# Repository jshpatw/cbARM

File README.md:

# cbARM (Cheese Burger ARM)

A 5-DOF (Degrees of Freedom) robot arm designed for high scalability, low cost, and ease of assembly using common makerspace materials.

## Why did i make this?

I always wanted an interactable robotic arm. But, online, the cheap ones cant lift any substancial weight and the good ones are very unaffordable. Most arms also came in fixed sizes and usally had a short range of motion. By making this prodject, I hope to adress theese 3 problems.

## Project Overview

The cbARM project aims to recreate industry-standard robot arm functionality using affordable, accessible components. By utilizing NEMA 17 motors, 3D-printed planetary gearboxes, a fully 3d printed conical stylle thrust bearing, and 2020 aluminum extrusions, this project provides a modular, affordable, and highly repairable alternative to commercial robotic systems.

## Target Features

* 5 Degrees of Freedom for full spatial maneuverability.
* Accessible build requiring no specialized machining.
* Modular design utilizing 2020 aluminum extrusions for variable arm lengths.
* Modular electronics; using female sockets soldered onto the pcb for "hot swapping" and easy electronics replacement.
* Scalable architecture for easy repair and upgrades.

## [Bill of Materials (BOM)]([url](https://github.com/jshpatw/cbARM/blob/main/BOM.csv))
u can find the bom in the repo via BOM.csv 

## Assembly and CAD Files

All STL files required for 3D printing the chassis and planetary gearboxes are available in the `/stl` directory of this repository. Refer to the pictures in journal.md portion for more complex parts and to see how I went about making things

* Recommended Material: PETG; 3 or more wall loops 20% minimum density 100% for gears and parts holding torque and gyroid pattern for structural rigidity and heat resistance (feel free to use PLA and other settings to test fitments).
* Hardware: Ensure all M3 heat-set inserts are installed prior to joining arm segments. 
* Bearings: Ensure 10x5x4mm bearings are seated with light pressure to avoid binding within 3D-printed pockets.
* Remember to practice safety when soldering parts and make sure to get extras and expect electronic defects.

Above is are pictures of the final PCB design for the prodject as of now. I reccomend using solder on female sockets to achive the electronic modularity. ensure u plug the 24V cables the right way as to not fry the board...

 The J0 objects mainly feature:
* Mounting holes for the 2020 extrution
* A vertical mount for the nema 17 42HS60
* 16:1 planetary reducers
* A 160mm 16 pin thrust bearing inspired by Logic [Planets work]([url](https://thangs.com/designer/logicalplanet/3d-model/Lazy%20Susan%20160%20v3.0-1514462))

He also has a youtube video in that link, I recommend watching his videos to better understand the mechanics and how to assemble that specific part.

 The J1 objects feature:
* A horizontal mount for the nema 17 hs 60 motor
* A 64:1 planetary gearbox
* Specialized thick gears to hendle the high torque setup
* A ring gear with a 2020 extrution mount for torque output

Above shows how the arm should look like after the 3d printed parts are assembled. (note that wires and electronics arent shown in this picture.

I made a document specially for assembly instructions at assembly guide.md in the repo for more in depth instructions and for the rest of the parts.

## Firmware and Control
 
* Status: Development in progress. 
* Firmware: To be updated.
* Control Interface: To be updated.

DISCLAIMER: the code is still physically untested so joints may move not as intended

## Future Roadmap

* Integration of Inverse Kinematics (IK) libraries.
* Development of end-effector/gripper attachments.
* Optimization of planetary gearbox backlash and tolerances.

## Extra info
* The CAD softwares used to make the prodject are KiCad and Fusion360 on education license
* Im using a p2s for prototyping and printing parts
* I also used pla to test initial fitments and tolerances
* I used old arduino code as reference and made the scripts on vs code and double checked with chatgpt
### Links & sources:
* https://thangs.com/designer/logicalplanet/3d-model/Lazy%20Susan%20160%20v3.0-1514462
* https://www.youtube.com/watch?v=S1EmJKU_IJU
* https://makerworld.com/en/models/2686085-planetary-gearbox-nema-17-1-16

## Feedback

Im currently doing everything solo so im open for advice and would appreciate feedback regarding anything in the prodject. 

## License

This project is licensed under the MIT License.

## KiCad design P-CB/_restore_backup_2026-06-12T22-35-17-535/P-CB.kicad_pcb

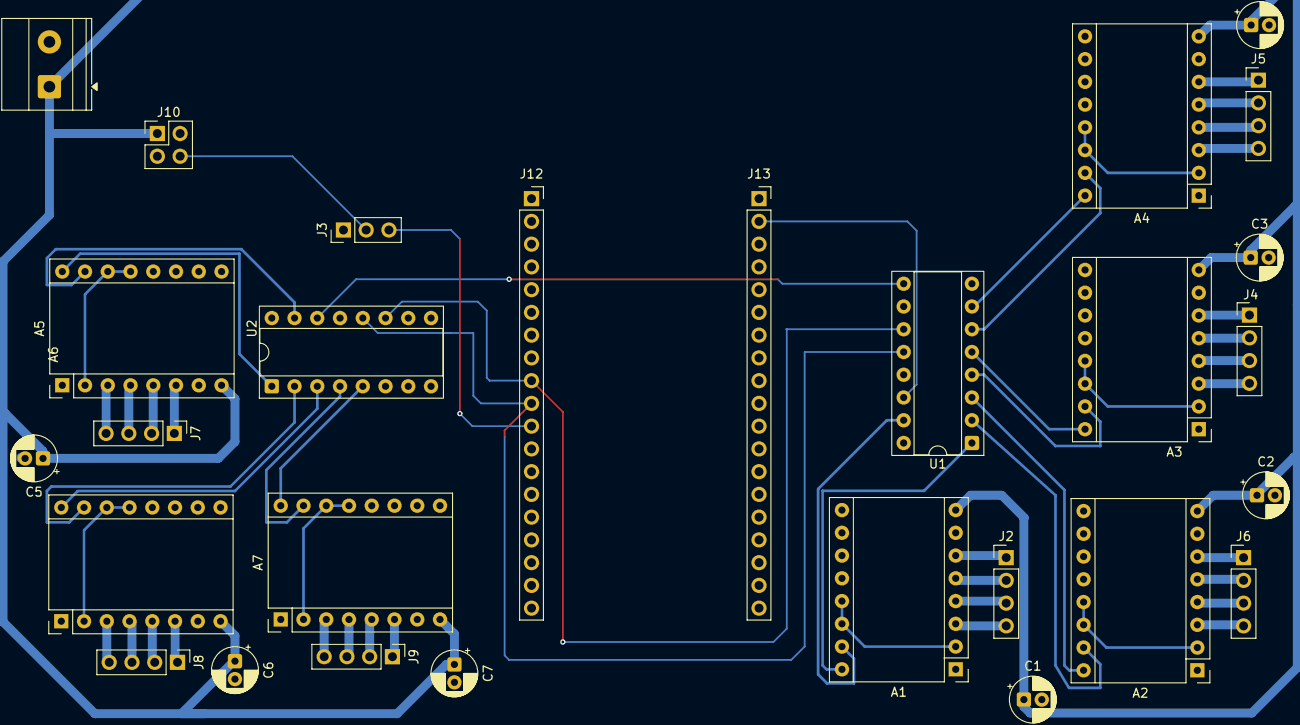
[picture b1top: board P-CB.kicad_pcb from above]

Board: 2 copper layers, 28 parts (0 on the bottom side), 51 nets.

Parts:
A1, A2, A3, A4, A5, A6, A7: Pololu_Breakout_A4988; Pololu_Breakout-16_15.2x20.3mm
C1, C2, C3, C4, C5, C6, C7: C_Polarized; CP_Radial_D5.0mm_P2.00mm
J2, J4, J5, J6, J7, J8, J9: Conn_01x04_Pin; PinHeader_1x04_P2.54mm_Vertical
J3: Conn_01x03; PinHeader_1x03_P2.54mm_Vertical
J10: Conn_02x02_Counter_Clockwise; PinHeader_2x02_P2.54mm_Vertical
J11: Conn_01x02_Pin; TerminalBlock_Phoenix_MKDS-1,5-2_1x02_P5.00mm_Horizontal
J12, J13: Conn_01x19; PinSocket_1x19_P2.54mm_Vertical
U1, U2: 74HC595; DIP-16_W7.62mm_Socket

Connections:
+5V: J3.2, J10.4, J13.1
+24V: A1.8 (VMOT), A2.8 (VMOT), A3.8 (VMOT), A4.8 (VMOT), A5.8 (VMOT), A6.8 (VMOT), A7.8 (VMOT), C1.1, C2.1, C3.1, C4.1, C5.1, C6.1, C7.1, J10.1, J11.1
/3.3V_global: A1.2 (VDD), A1.13 (~RESET), A1.14 (~SLEEP), A2.2 (VDD), A2.13 (~RESET), A2.14 (~SLEEP), A3.2 (VDD), A3.13 (~RESET), A3.14 (~SLEEP), A4.2 (VDD), A4.13 (~RESET), A4.14 (~SLEEP), A5.2 (VDD), A5.13 (~RESET), A5.14 (~SLEEP), A6.2 (VDD), A6.13 (~RESET), A6.14 (~SLEEP), A7.2 (VDD), A7.13 (~RESET), A7.14 (~SLEEP), J12.1, U1.10 (~SRCLR), U1.16 (VCC), U2.10 (~SRCLR), U2.16 (VCC)
/DATA_CASCADE: U1.9 (QH'), U2.14 (SER)
/I2S_BCK: J12.9, U1.11 (SRCLK), U2.11 (SRCLK)
/I2S_DATA: J13.2, U1.14 (SER)
/I2S_LATCH: J12.10, U1.12 (RCLK), U2.12 (RCLK)
/SERVO_PWM: J3.3, J12.11
GND: A1.1 (GND), A1.7 (GND), A2.1 (GND), A2.7 (GND), A3.1 (GND), A3.7 (GND), A4.1 (GND), A4.7 (GND), A5.1 (GND), A5.7 (GND), A6.1 (GND), A6.7 (GND), A7.1 (GND), A7.7 (GND), J3.1, J10.2, J10.3, J11.2, J13.19, U1.8 (GND), U1.13 (~OE), U2.8 (GND), U2.13 (~OE)
unnamed: A1.4 (1A), J2.3
unnamed: A1.3 (1B), J2.4
unnamed: A1.5 (2A), J2.2
unnamed: A1.6 (2B), J2.1
unnamed: A1.16 (DIR), U1.1 (QB)
unnamed: A1.15 (STEP), U1.15 (QA)
unnamed: A2.4 (1A), J6.3
unnamed: A2.3 (1B), J6.4
unnamed: A2.5 (2A), J6.2
unnamed: A2.6 (2B), J6.1
unnamed: A2.16 (DIR), U1.3 (QD)
unnamed: A2.15 (STEP), U1.2 (QC)
unnamed: A3.4 (1A), J4.3
unnamed: A3.3 (1B), J4.4
unnamed: A3.5 (2A), J4.2
unnamed: A3.6 (2B), J4.1
unnamed: A3.16 (DIR), U1.5 (QF)
unnamed: A3.15 (STEP), U1.4 (QE)
unnamed: A4.4 (1A), J5.3
unnamed: A4.3 (1B), J5.4
unnamed: A4.5 (2A), J5.2
unnamed: A4.6 (2B), J5.1
unnamed: A4.16 (DIR), U1.7 (QH)
unnamed: A4.15 (STEP), U1.6 (QG)
unnamed: A5.4 (1A), J7.3
unnamed: A5.3 (1B), J7.4
unnamed: A5.5 (2A), J7.2
unnamed: A5.6 (2B), J7.1
unnamed: A5.16 (DIR), U2.1 (QB)
unnamed: A5.15 (STEP), U2.15 (QA)
unnamed: A6.4 (1A), J8.3
unnamed: A6.3 (1B), J8.4
unnamed: A6.5 (2A), J8.2
unnamed: A6.6 (2B), J8.1
unnamed: A6.16 (DIR), U2.3 (QD)
unnamed: A6.15 (STEP), U2.2 (QC)
unnamed: A7.4 (1A), J9.3
unnamed: A7.3 (1B), J9.4
unnamed: A7.5 (2A), J9.2
unnamed: A7.6 (2B), J9.1
unnamed: A7.16 (DIR), U2.5 (QF)
unnamed: A7.15 (STEP), U2.4 (QE)

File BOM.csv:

"Category","Reference/Item","Qty","Value/Spec","Manufacturer/Notes"
"Electronics","A1-A7","7","Pololu_A4988","Motor Drivers"
"Electronics","C1-C7","7","100uF_35V","Electrolytic Capacitor"
"Electronics","J2,J4-J9","7","Conn_01x04","Header Pins"
"Electronics","J3","1","Conn_01x03","Header Pins"
"Electronics","J10","1","Mini360_Module","Buck Converter"
"Electronics","J11","1","2_Pin_Term_Block","5.00mm Pitch"
"Electronics","J12,J13","2","Conn_01x19","Pin Socket"
"Electronics","U1,U2","2","74HC595","Shift Register"
"Electronics","Power Supply","1","24V 15A","Main System PSU"
"Mechanical","Stepper Motors","7","NEMA 17 (42HS60)","1.8 Degree Step"
"Mechanical","Bearings","100","MR105ZZ (10x5x4mm)","Steel Shielded"
"Mechanical","Screws","100","M3 x 10mm","Socket Head Cap"
"Mechanical","Heat-Set Inserts","100","M3 Brass Insert","For PETG"
"Mechanical","Filament","3kg","PETG 1.75mm","Chassis Material"

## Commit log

2026-06-20 pcb stuff!
2026-06-20 most of the stls
2026-06-20 zine
    im sorry for for my lack of design skilss
2026-06-20 Add BOM.csv with components and specifications
2026-06-20 Enhance README with project details and instructions
    Added detailed project overview, target features, bill of materials, assembly instructions, firmware status, future roadmap, and feedback section to README.
2026-06-20 Include PCB design images and project status update
    Added images of the final PCB design and updated project status.
2026-06-20 Update README with PCB design images and status
    Added a note about the final PCB design and firmware status.
2026-06-20 Add Firmware and Control section to README
    Added section for Firmware and Control status updates.
2026-06-20 Update README with PCB and arm assembly images
    Added images of the final PCB design and 3D printed arm assembly.
2026-06-21 Update README with modular electronics details
    Added information about modular electronics and provided recommendations for soldering female sockets to achieve electronic modularity.
2026-06-22 Revise README with material and assembly details
    Updated material specifications and added details about J0 objects.
2026-06-22 Enhance README with assembly video recommendation
    Added a recommendation to watch a YouTube video for better understanding of assembly.
2026-06-25 Add assembly guide for cbARM PCB and housing
    This guide provides detailed instructions for assembling the cbARM control module, including PCB and electronics setup, connector configurations, mounting, and pre-power inspection steps.
2026-06-25 Enhance assembly guide for J0 parts
    Expanded assembly instructions for J0 parts, including details on aluminum extrusions and motor mounting.
2026-06-25 Update assembly guide with j0 component details
    Clarified assembly instructions for j0 component, including recommendations for aluminum extrusion lengths and motor mounting.
2026-06-25 Enhance assembly guide with thrust bearing instructions
    Added detailed instructions for assembling the thrust bearing and j0 components, including references to specific STL files and images for clarity.
2026-06-25 Revise thrust bearing assembly instructions
    Updated assembly instructions for thrust bearing and j0 components, including new image references.
2026-06-26 zine
2026-06-26 Rename Copy of Chese burger-1.pdf to Chese burger.pdf
2026-06-26 Replace image of cbARM with updated version
    Updated image reference in README.md to a new source.
2026-06-27 Document J1 assembly instructions and parts list
    Added detailed instructions for assembling J1 parts, including a list of components and assembly steps.
2026-06-27 Enhance assembly guide with J2 supports and parts
    Added detailed instructions for J2 supports and parts assembly.
2026-06-27 Update BOM.csv to correct component description
2026-06-27 Fix typos in assembly guide for bearing sizes
2026-06-28 Add Google Drive link for CAD files
2026-06-28 Add files via upload
    firmware for testing upon assembly
2026-06-28 Fix CSV header formatting in BOM.csv
2026-06-28 Duplicate entries added to BOM.csv
    Added duplicate entries for various components in BOM.csv.
2026-06-28 Revise BOM with updated item specifications and pricing
    Updated BOM.csv to include new pricing and item details.
2026-06-28 Revise BOM section and add assembly guide reference
    Updated Bill of Materials section and added assembly instructions note.
2026-06-28 Add second image to README for cbARM project
    Added a second image of the cbARM robot arm to the README.
2026-06-28 Track CAD extensions with LFS and add files
